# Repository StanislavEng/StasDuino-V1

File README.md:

# StasDuino-V1
A simple PCB project of an Arduino Clone. This was a "project" I chose to do to learn some of the steps required in PCB design.
This encompassed looking up components, using datasheets to create footprints, creating the schematics and laying them on the actual (software) PCB.

This project was done in Autodesk Eagle because I had it installed from earlier and is probably useful to learn anyway. 

For V1, the main components such as the ATMega, the serial converter and some resistors and MOSFETs were made by me.  
The rest of the parts I grabbed from libraries because I wanted to get into the real meat of the task. 

The schematic, at least in regards to wiring up the components related to the ATMega, were done by referring to the datasheet and the  
Atmel "Hardware Design Considerations" paper. The rest I looked at the official Arduino schematic to get some (better practices) understanding  
of how they did it and a bit of why. 

The real time crunch, apparently, was creating the actual layout on the PCB. Laying out the pieces in a way that allowed for better tracing was  
actually a painful but interesting learning experience. As a result, I also created "3" revisions to try to improve the layout. 

## Rev 1:
My original board design, learning to create traces and place down parts, and,  
as a result does not have the best of tracing. 

## Rev 2: 
Looking at what the autotrace creates and seeing what is *maybe* possible, best practice wise,  
as in what kind of designs (regardig traces) is allowed.

## Rev 3: 
Recreating traces and changing some part orientation to create a overall better designed board.  
Not sure if actually better but I felt more proud.

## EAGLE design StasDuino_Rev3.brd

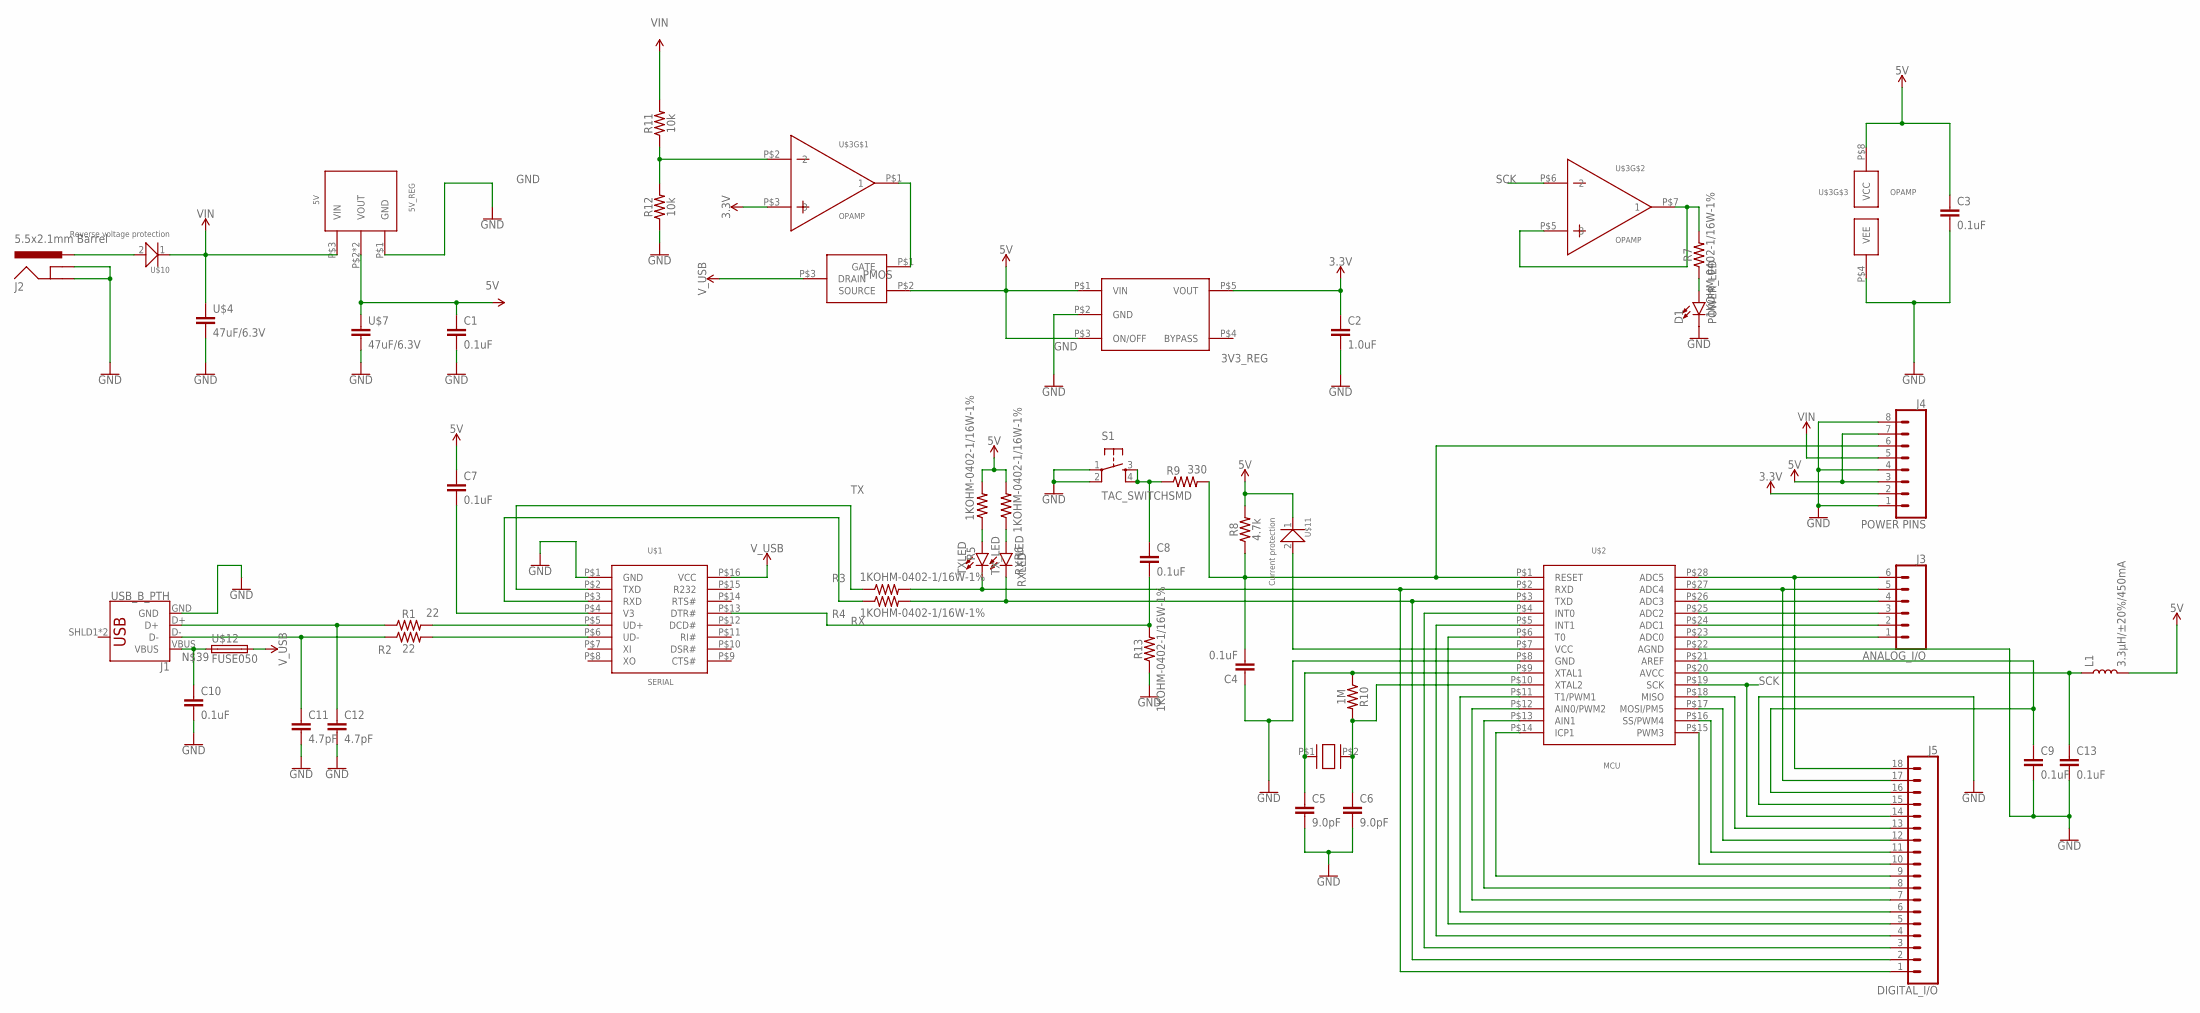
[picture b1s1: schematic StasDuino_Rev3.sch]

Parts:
3V3_REG: 3V3; 3V3-REGULATOR
5V_REG: 5V; 5V_REGULATOR
C1, C3, C4, C7, C8, C9, C10, C13: 0.1uF; 0402
C2: 1.0uF; 0402
C5, C6: 9.0pF; 0603
C11, C12: 4.7pF; 0603
D1: POWER_LED; LED-0603
J1: USB_B_PTH; USB-B-PTH
J2: 5.5x2.1mm Barrel; POWER_JACK_SMD
J3: ANALOG_I/O; 1X06_NO_SILK
J4: POWER PINS; 1X08_NO_SILK
J5: DIGITAL_I/O; 1X18_NO_SILK
L1: 3.3µH/±20%/450mA; 0805
PMOS: PMOS; PMOSFET
R1, R2: 22; 0402
R3, R4, R5, R6, R7, R13: 1KOHM-0402-1/16W-1%; 0402
R8: 4.7k; 0603
R9: 330; 0603
R10: 1M; 0603
R11, R12: 10k; 0402
RXLED: RX_LED; LED-0603
S1: TAC_SWITCHSMD; TACTILE-SWITCH-SMD
TXLED: TX_LED; LED-0603
U$1: SERIAL; CH340G/C
U$2: MCU; ATMEGA328P
U$3: OPAMP; DUAL_OPAMP
U$4, U$7: 47uF/6.3V; 0805
U$8: 16MHz; CRYSTAL
U$10: Reverse voltage protection; 0402
U$11: Current protection; 0402
U$12: FUSE050; MF-SMDF050

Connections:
3.3V: 3V3_REG.P$5 (VOUT), C2.1, J4.2, U$3.P$3 (3)
5V: 3V3_REG.P$1 (VIN), 3V3_REG.P$3 (ON/OFF), 5V_REG.P$2 (VOUT), 5V_REG.P$2B (VOUT), C1.1, C3.1, C7.1, J4.3, J4.7, L1.2, PMOS.P$2 (SOURCE), R5.2, R6.2, R8.2, U$3.P$8 (VCC), U$7.1, U$11.1
D+: R1.2, U$1.P$5 (UD+)
GND: 3V3_REG.P$2 (GND), 5V_REG.P$1 (GND), C1.2, C2.2, C3.2, C4.1, C5.2, C6.2, C9.2, C10.2, C11.2, C12.2, C13.2, D1.C, J1.GND, J2.GND (GNDBREAK), J2.P$4 (GND), J4.1, J4.4, J4.8, J5.15, R12.1, R13.1, S1.1, S1.2, U$1.P$1 (GND), U$2.P$8 (GND), U$2.P$22 (AGND), U$3.P$4 (VEE), U$4.2, U$7.2
unnamed: C12.1, J1.D+, R1.1
unnamed: C4.2, J4.6, R8.1, R9.2, U$2.P$1 (RESET)
unnamed: C11.1, J1.D-, R2.1
unnamed: R2.2, U$1.P$6 (UD-)
unnamed: J5.2, R4.2, RXLED.C, U$2.P$3 (TXD)
unnamed: J5.1, R3.2, TXLED.C, U$2.P$2 (RXD)
unnamed: C8.1, R9.1, S1.3, S1.4
unnamed: R5.1, TXLED.A
unnamed: R6.1, RXLED.A
unnamed: D1.A, R7.1
unnamed: R7.2, U$3.P$5 (3), U$3.P$7 (1)
unnamed: C5.1, R10.1, U$2.P$9 (XTAL1), U$8.P$1
unnamed: C6.1, R10.2, U$2.P$10 (XTAL2), U$8.P$2
unnamed: J3.6, J5.18, U$2.P$28 (ADC5)
unnamed: PMOS.P$1 (GATE), U$3.P$1 (1)
unnamed: J2.VIN0 (PWR), U$10.2
unnamed: R11.1, R12.2, U$3.P$2 (2)
unnamed: C7.2, U$1.P$4 (V3)
unnamed: C8.2, R13.2, U$1.P$13 (DTR#)
unnamed: U$2.P$7 (VCC), U$11.2
unnamed: J3.5, J5.17, U$2.P$27 (ADC4)
unnamed: J3.4, U$2.P$26 (ADC3)
unnamed: J3.3, U$2.P$25 (ADC2)
unnamed: J3.2, U$2.P$24 (ADC1)
unnamed: J3.1, U$2.P$23 (ADC0)
unnamed: J5.3, U$2.P$4 (INT0)
unnamed: J5.4, U$2.P$5 (INT1)
unnamed: J5.5, U$2.P$6 (T0)
unnamed: J5.6, U$2.P$11 (T1/PWM1)
unnamed: J5.7, U$2.P$12 (AIN0/PWM2)
unnamed: J5.8, U$2.P$13 (AIN1)
unnamed: J5.9, U$2.P$14 (ICP1)
unnamed: J5.10, U$2.P$15 (PWM3)
unnamed: J5.11, U$2.P$16 (SS/PWM4)
unnamed: J5.12, U$2.P$17 (MOSI/PM5)
unnamed: J5.13, U$2.P$18 (MISO)
unnamed: C9.1, J5.16, U$2.P$21 (AREF)
unnamed: C10.1, J1.VBUS, U$12.1
unnamed: C13.1, L1.1, U$2.P$20 (AVCC)
RX: R4.1, U$1.P$3 (RXD)
SCK: J5.14, U$2.P$19 (SCK), U$3.P$6 (2)
TX: R3.1, U$1.P$2 (TXD)
VIN: 5V_REG.P$3 (VIN), J4.5, R11.2, U$4.1, U$10.1
V_USB: PMOS.P$3 (DRAIN), U$1.P$16 (VCC), U$12.2

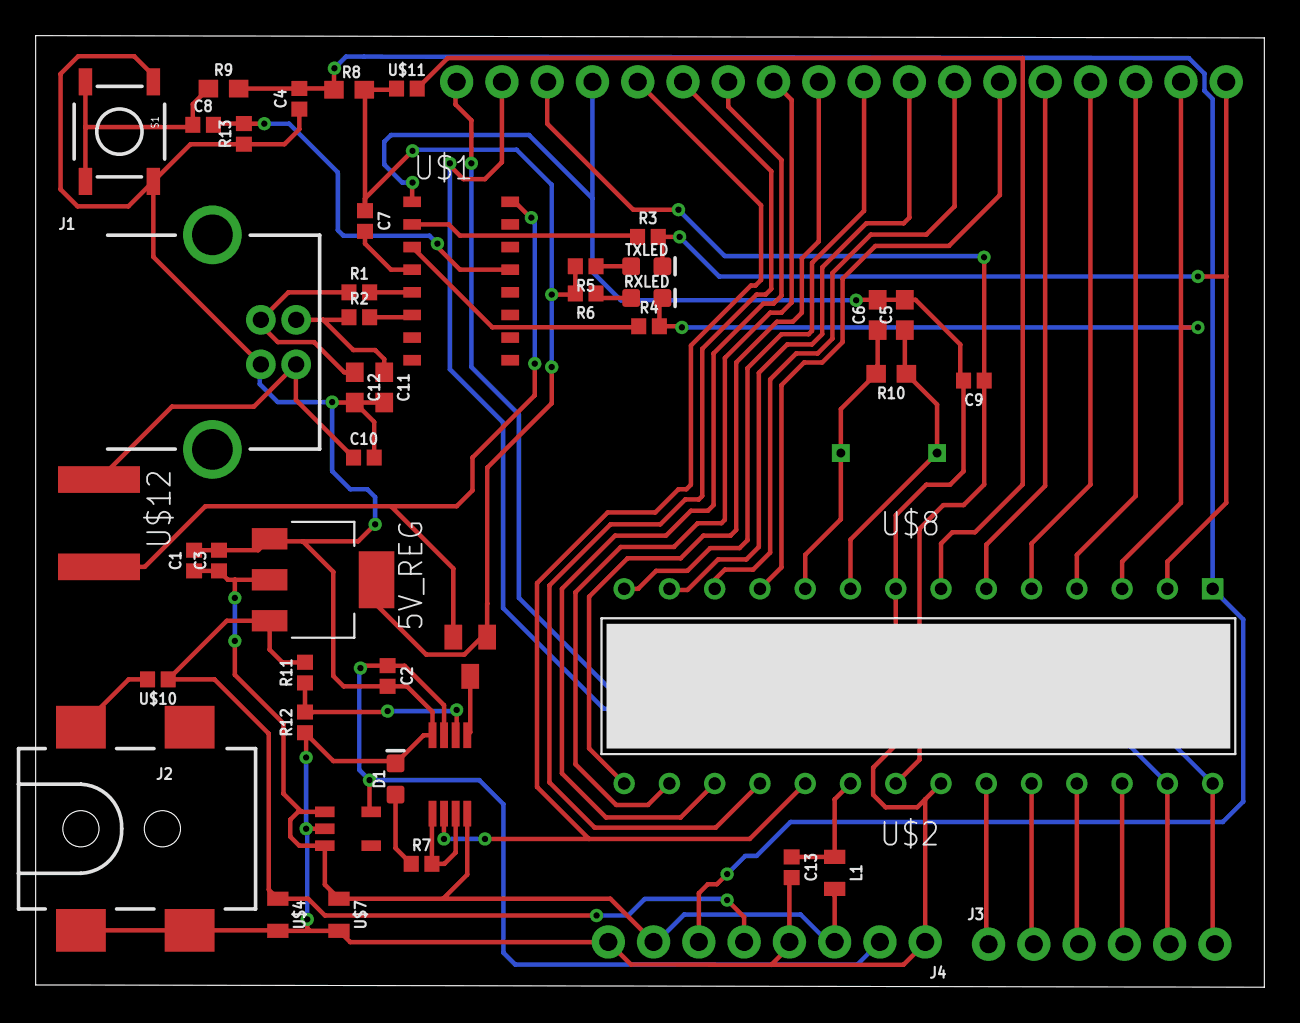
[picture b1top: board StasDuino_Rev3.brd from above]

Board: 2 copper layers, 68.9 x 53.4 mm, 48 parts (0 on the bottom side), 48 nets.

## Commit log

2021-03-03 Adding in some custom footprints
2021-03-13 A weeks worth of learning/understanding concepts/searching and making parts
2021-03-14 There's too many items omg
2021-03-16 Starting schematic, ignoring some of the parts I don't have finished
2021-03-16 Adding ignore file for .s# files I hope
2021-03-16 Checking gitignore
2021-03-16 Checking gitignore again
2021-03-16 Checking gitignore last tiome
2021-03-16 Checking directory hiding
2021-03-17 Finished up wiring the schematic, hopefully
2021-03-20 Board mostly complete
2021-03-20 Almost done the traces. Could do with a V1 Rev 2 remake all traces from scratch
2021-03-22 Finished Rev1, created an autotrace version (rev2) and remaking traces Rev3
2021-03-22 Finished Rev3. Added a trace I missed and made them make more sense. V1 is done

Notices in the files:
parts and their libraries:
SparkFun-Capacitors: Licensing: Creative Commons ShareAlike 4.0 International - https://creativecommons.org/licenses/by-sa/4.0
